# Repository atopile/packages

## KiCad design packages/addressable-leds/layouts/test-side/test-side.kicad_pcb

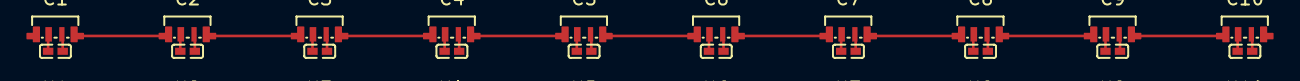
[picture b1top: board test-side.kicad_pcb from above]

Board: 2 copper layers, 20 parts (0 on the bottom side), 11 nets.

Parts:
C1, C2, C3, C4, C5, C6, C7, C8, C9, C10: 100nF ±10% 16V X7R; C0402
U1, U2, U3, U4, U5, U6, U7, U8, U9, U10: LED-SMD_4P-L3.5-W1.6_SK6805SIDE-G-001

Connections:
DOUT: U1.1, U2.4
DOUT-1: U2.1, U3.4
DOUT-2: U3.1, U4.4
DOUT-3: U4.1, U5.4
DOUT-4: U5.1, U6.4
DOUT-5: U6.1, U7.4
DOUT-6: U7.1, U8.4
DOUT-7: U8.1, U9.4
DOUT-8: U9.1, U10.4
gnd: C1.2, C2.2, C3.2, C4.2, C5.2, C6.2, C7.2, C8.2, C9.2, C10.2, U1.2, U2.2, U3.2, U4.2, U5.2, U6.2, U7.2, U8.2, U9.2, U10.2
hv: C1.1, C2.1, C3.1, C4.1, C5.1, C6.1, C7.1, C8.1, C9.1, C10.1, U1.3, U2.3, U3.3, U4.3, U5.3, U6.3, U7.3, U8.3, U9.3, U10.3

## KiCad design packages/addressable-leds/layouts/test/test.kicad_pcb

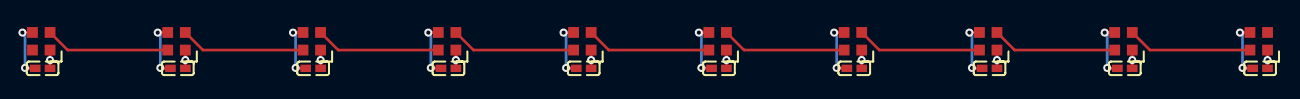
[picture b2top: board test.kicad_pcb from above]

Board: 2 copper layers, 20 parts (0 on the bottom side), 11 nets.

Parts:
C1, C2, C3, C4, C5, C6, C7, C8, C9, C10: 100nF ±10% 16V X7R; C0402
U1, U2, U3, U4, U5, U6, U7, U8, U9, U10: LED-SMD_4P-L2.0-W2.0-BR

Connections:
-DOUT-0: U1.2, U2.4
-DOUT-1: U2.2, U3.4
-DOUT-2: U3.2, U4.4
-DOUT-3: U4.2, U5.4
-DOUT-4: U5.2, U6.4
-DOUT-5: U6.2, U7.4
-DOUT-6: U7.2, U8.4
-DOUT-7: U8.2, U9.4
-DOUT-8: U9.2, U10.4
gnd: C1.2, C2.2, C3.2, C4.2, C5.2, C6.2, C7.2, C8.2, C9.2, C10.2, U1.3, U2.3, U3.3, U4.3, U5.3, U6.3, U7.3, U8.3, U9.3, U10.3
hv: C1.1, C2.1, C3.1, C4.1, C5.1, C6.1, C7.1, C8.1, C9.1, C10.1, U1.1, U2.1, U3.1, U4.1, U5.1, U6.1, U7.1, U8.1, U9.1, U10.1

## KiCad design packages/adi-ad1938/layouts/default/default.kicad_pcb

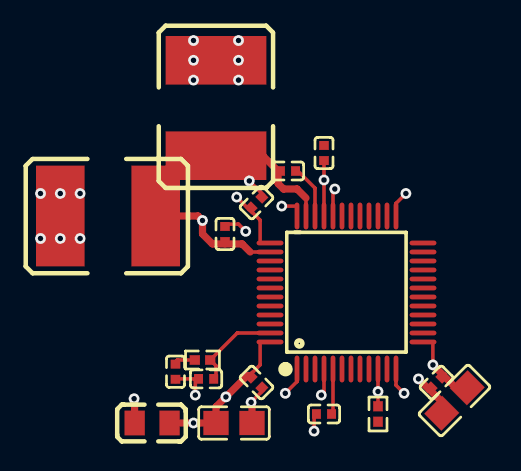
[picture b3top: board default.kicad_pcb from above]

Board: 2 copper layers, 17 parts (0 on the bottom side), 8 nets.

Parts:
C1, C2, C3, C4, C5, C8, C12: 100nF; C0402
C6: 5.6nF; C0402
C7: 390pF; C0402
C9, C13: 47µF; CAP-SMD_L6.1-W5.3-L-1
C10, C11: 10µF; C0805
L1: L 6.8µH; L0805
R1: 560Ω; R0402
R2: 100kΩ; R0402
U1: LQFP-48_L7.0-W7.0-P0.50-LS9.0-BL

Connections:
c1-power-hv: C6.1, R1.2
c2-power-hv: C7.1, R1.1, U1.47
c_bulk-power-hv: C8.1, C9.1, U1.38
c_bulk-power-hv-1: C12.1, C13.1, U1.35
hv: C1.1, C2.1, C3.1, C4.1, C10.1, L1.2, U1.5, U1.33, U1.37, U1.48
lv: C1.2, C2.2, C3.2, C4.2, C5.2, C6.2, C7.2, C8.2, C9.2, C10.2, C11.2, C12.2, C13.2, R2.2, U1.1, U1.4, U1.12, U1.25, U1.32, U1.34, U1.36
nPD_nRST: R2.1, U1.10
power_io-hv: C5.1, C11.1, L1.1, U1.13
